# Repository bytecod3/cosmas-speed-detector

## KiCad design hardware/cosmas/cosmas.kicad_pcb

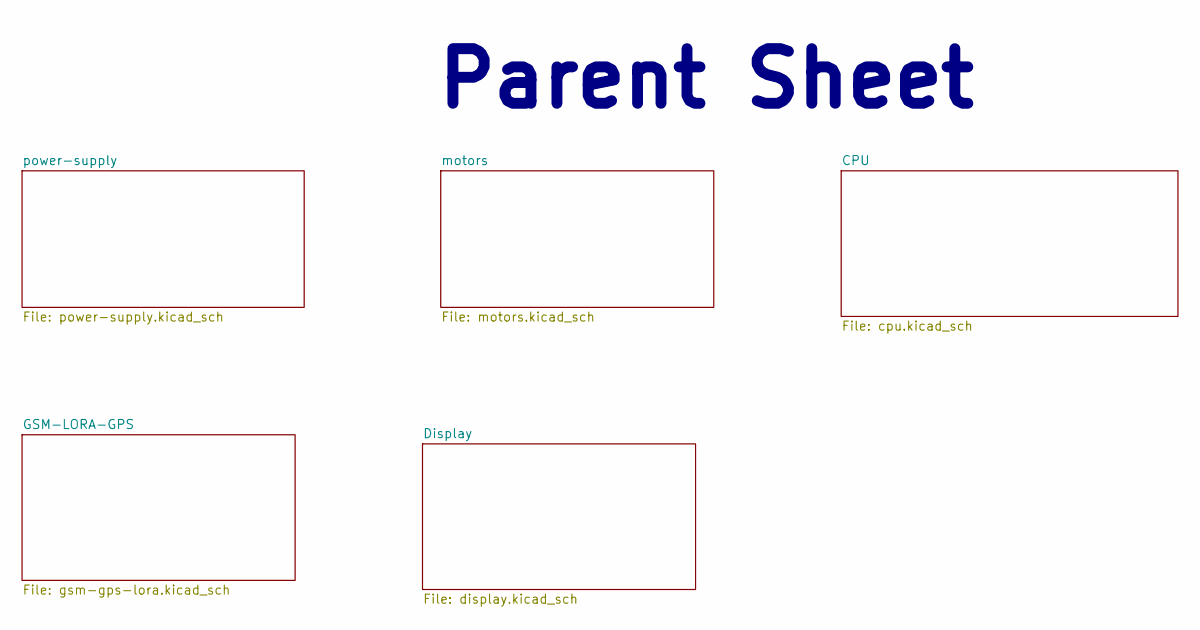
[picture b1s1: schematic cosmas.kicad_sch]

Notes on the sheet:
Parent Sheet

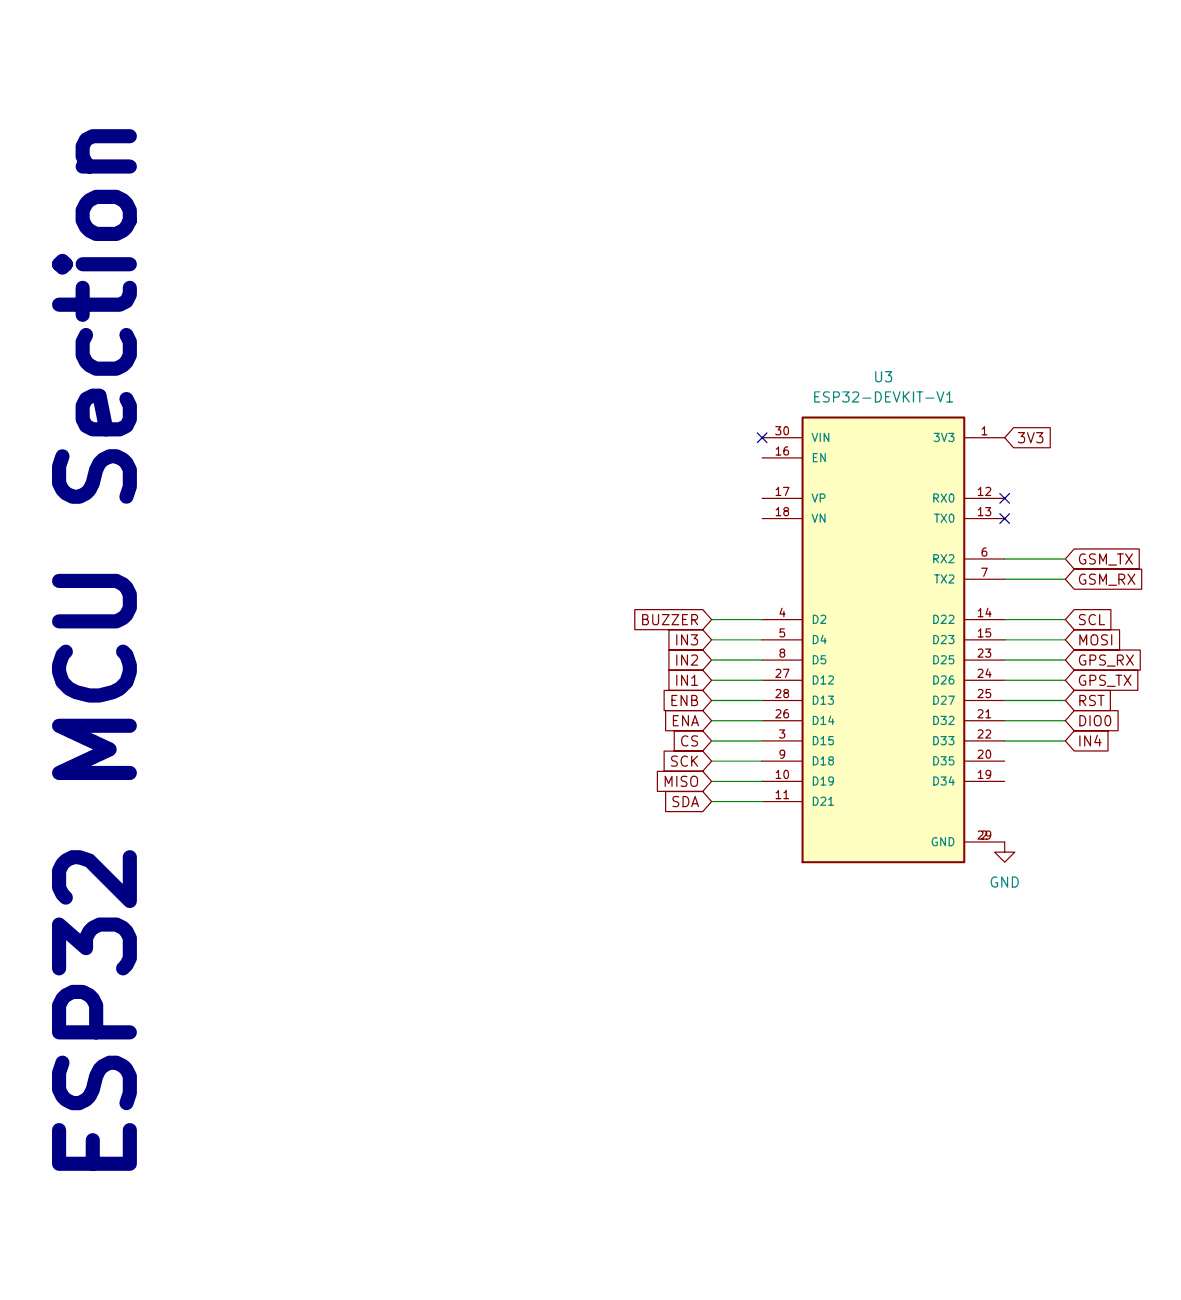
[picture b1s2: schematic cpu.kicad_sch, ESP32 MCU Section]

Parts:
U3: ESP32-DEVKIT-V1; MODULE_ESP32_DEVKIT_V1; PARTREV N/A

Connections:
3V3: U3.1 (3V3); also elsewhere on the board
BUZZER: U3.4 (D2); also elsewhere on the board
CS: U3.3 (D15); also elsewhere on the board
DIO0: U3.21 (D32); also elsewhere on the board
ENA: U3.26 (D14); also elsewhere on the board
ENB: U3.28 (D13); also elsewhere on the board
GND: U3.2 (GND), U3.29 (GND); also elsewhere on the board
GPS_RX: U3.23 (D25); also elsewhere on the board
GPS_TX: U3.24 (D26); also elsewhere on the board
GSM_RX: U3.7 (TX2); also elsewhere on the board
GSM_TX: U3.6 (RX2); also elsewhere on the board
IN1: U3.27 (D12); also elsewhere on the board
IN2: U3.8 (D5); also elsewhere on the board
IN3: U3.5 (D4); also elsewhere on the board
IN4: U3.22 (D33); also elsewhere on the board
MISO: U3.10 (D19); also elsewhere on the board
MOSI: U3.15 (D23); also elsewhere on the board
RST: U3.25 (D27); also elsewhere on the board
SCK: U3.9 (D18); also elsewhere on the board
SCL: U3.14 (D22); also elsewhere on the board
SDA: U3.11 (D21); also elsewhere on the board

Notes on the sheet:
ESP32 MCU Section

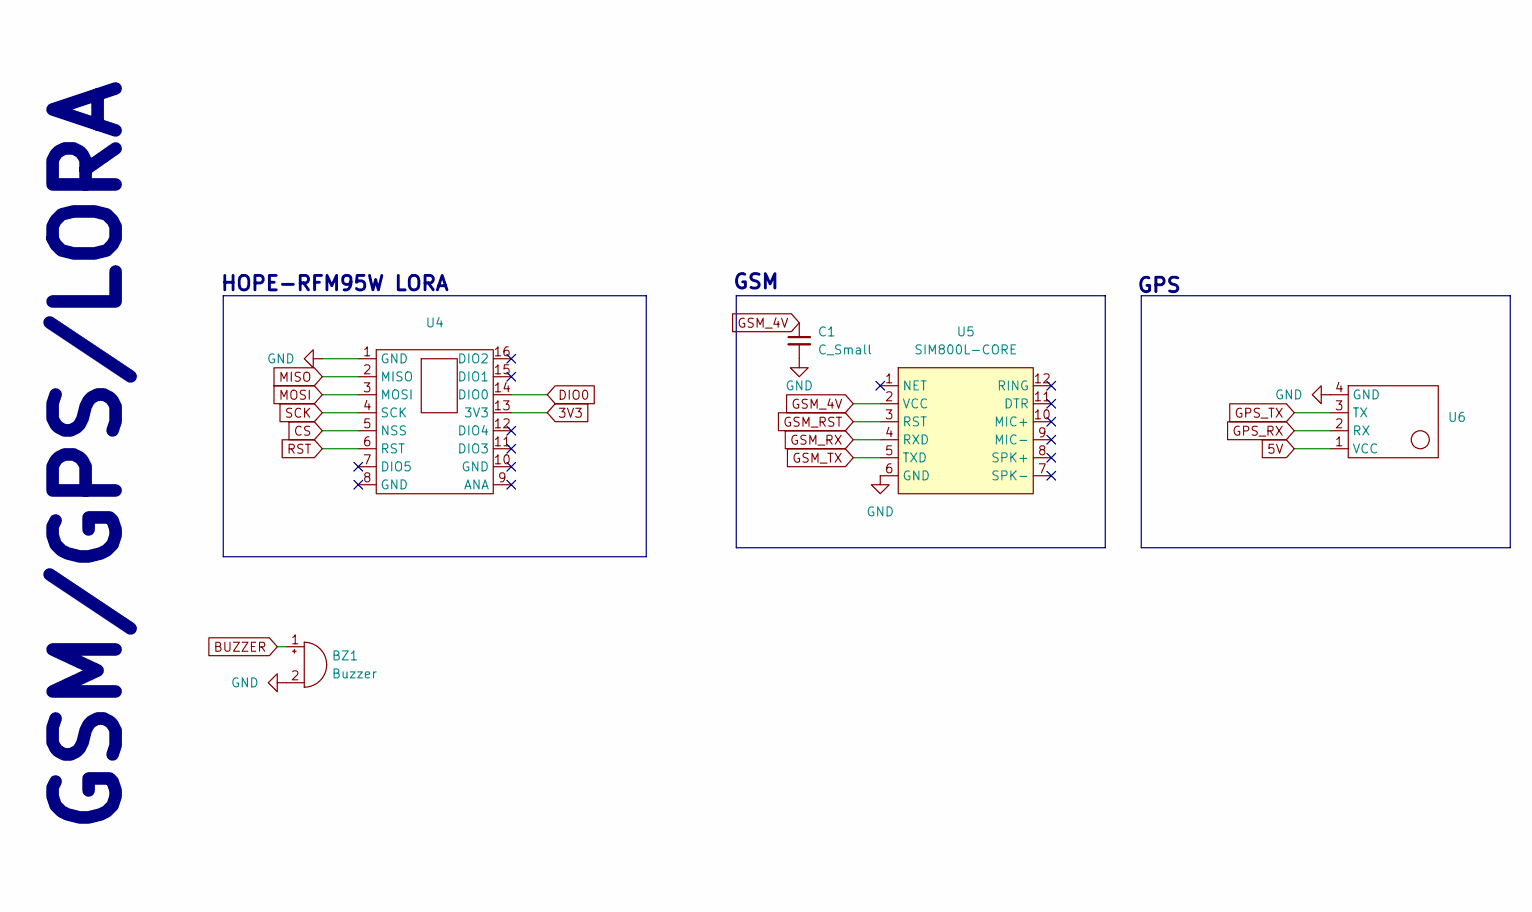
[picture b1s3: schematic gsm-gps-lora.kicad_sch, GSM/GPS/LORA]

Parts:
BZ1: Buzzer; MagneticBuzzer_PUI_AT-0927-TT-6-R
C1: C_Small; CP_Radial_D4.0mm_P2.00mm
U4: XCVR_RFM95W-915S2
U5: SIM800L-CORE
U6: NEO-6M-GPS-MODULE

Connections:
3V3: U4.13 (3V3); also elsewhere on the board
5V: U6.1 (VCC); also elsewhere on the board
BUZZER: BZ1.1 (+); also elsewhere on the board
CS: U4.5 (NSS); also elsewhere on the board
DIO0: U4.14 (DIO0); also elsewhere on the board
GND: BZ1.2 (-), C1.2, U4.1 (GND), U5.6 (GND), U6.4 (GND); also elsewhere on the board
GPS_RX: U6.2 (RX); also elsewhere on the board
GPS_TX: U6.3 (TX); also elsewhere on the board
GSM_4V: C1.1, U5.2 (VCC); also elsewhere on the board
GSM_RST: U5.3 (RST)
GSM_RX: U5.4 (RXD); also elsewhere on the board
GSM_TX: U5.5 (TXD); also elsewhere on the board
MISO: U4.2 (MISO); also elsewhere on the board
MOSI: U4.3 (MOSI); also elsewhere on the board
RST: U4.6 (RST); also elsewhere on the board
SCK: U4.4 (SCK); also elsewhere on the board

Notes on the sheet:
HOPE-RFM95W LORA
GPS
GSM
GSM/GPS/LORA

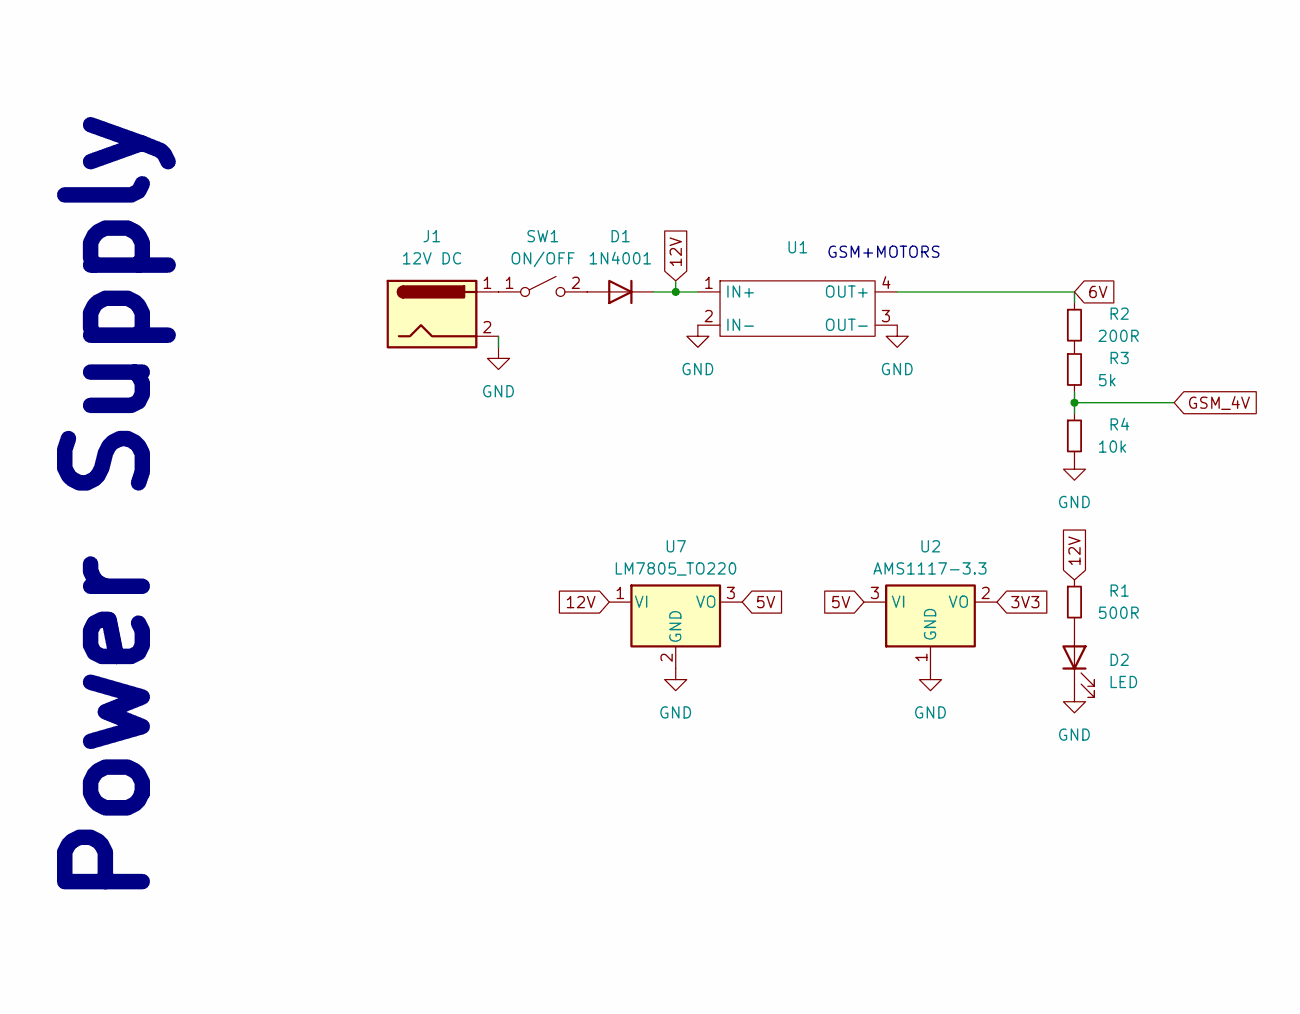
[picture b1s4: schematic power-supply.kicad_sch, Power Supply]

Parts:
D1: 1N4001; D_DO-41_SOD81_P10.16mm_Horizontal
D2: LED; LED_D3.0mm
J1: 12V DC; BarrelJack_Kycon_KLDX-0202-xC_Horizontal
R1: 500R; R_Axial_DIN0309_L9.0mm_D3.2mm_P15.24mm_Horizontal
R2: 200R; R_Axial_DIN0309_L9.0mm_D3.2mm_P15.24mm_Horizontal
R3: 5k; R_Axial_DIN0309_L9.0mm_D3.2mm_P15.24mm_Horizontal
R4: 10k; R_Axial_DIN0309_L9.0mm_D3.2mm_P15.24mm_Horizontal
SW1: ON/OFF; SW_Push_2P2T_Toggle_CK_PVA2OAH5xxxxxxV2
U1: LM2596-BUCK-CONVERTER
U2: AMS1117-3.3; SOT-223-3_TabPin2
U7: LM7805_TO220; TO-220-3_Vertical

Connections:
3V3: U2.2 (VO); also elsewhere on the board
5V: U2.3 (VI), U7.3 (VO); also elsewhere on the board
6V: R2.1, U1.4 (OUT+); also elsewhere on the board
12V: D1.1 (K), R1.1, U1.1 (IN+), U7.1 (VI)
GND: D2.1 (K), J1.2, R4.2, U1.2 (IN-), U1.3 (OUT-), U2.1 (GND), U7.2 (GND); also elsewhere on the board
GSM_4V: R3.2, R4.1; also elsewhere on the board
unnamed: D1.2 (A), SW1.2 (B)
unnamed: D2.2 (A), R1.2
unnamed: R2.2, R3.1
unnamed: J1.1, SW1.1 (A)

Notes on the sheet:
GSM+MOTORS
Power Supply

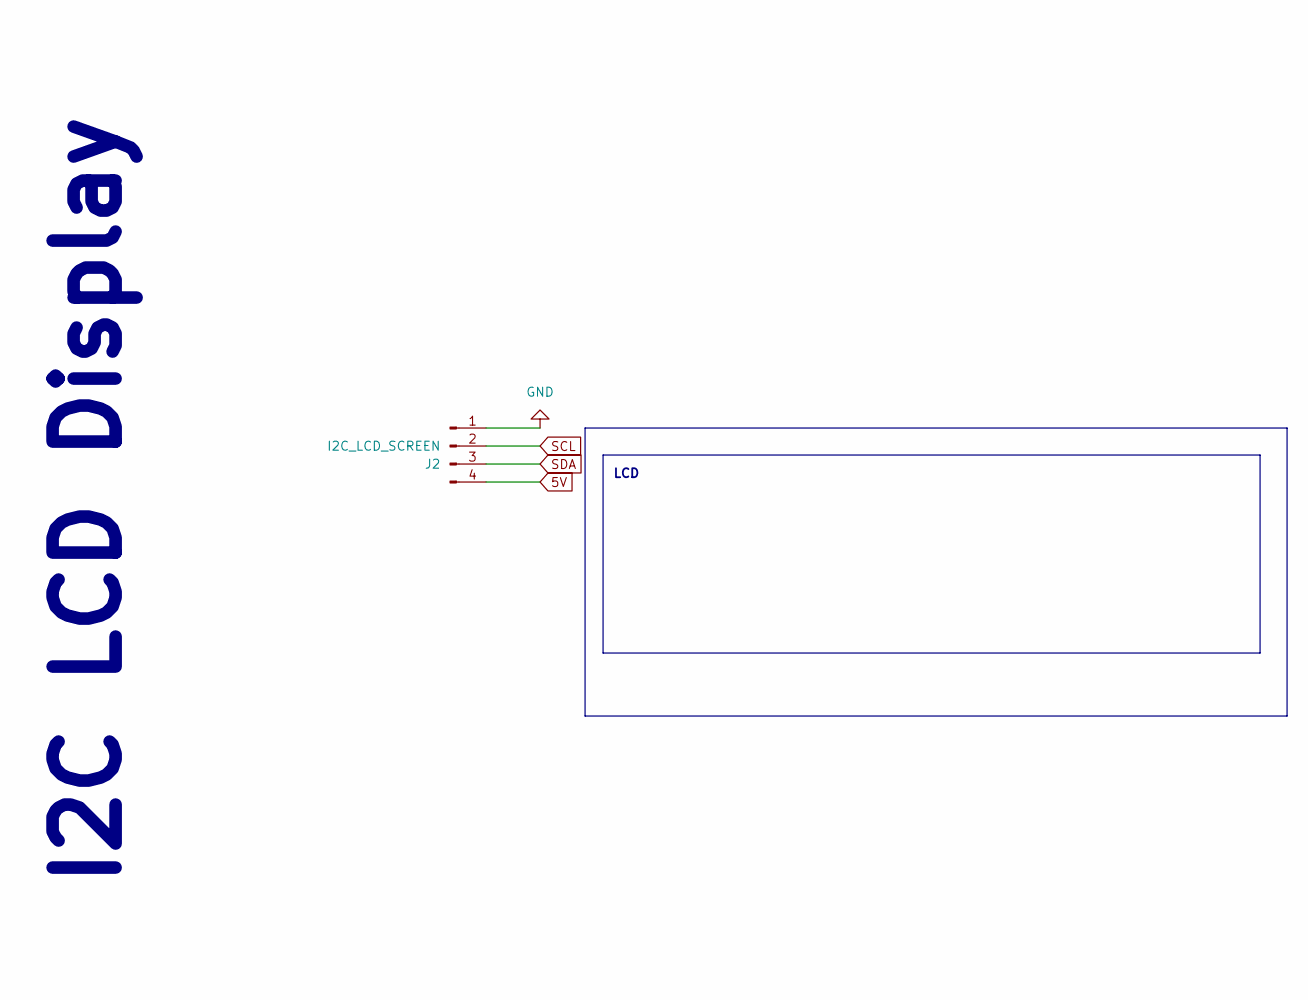
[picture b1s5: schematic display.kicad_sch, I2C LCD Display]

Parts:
J2: I2C_LCD_SCREEN; PinHeader_1x04_P2.54mm_Vertical

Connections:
5V: J2.4; also elsewhere on the board
GND: J2.1; also elsewhere on the board
SCL: J2.2; also elsewhere on the board
SDA: J2.3; also elsewhere on the board

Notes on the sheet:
LCD
I2C LCD Display

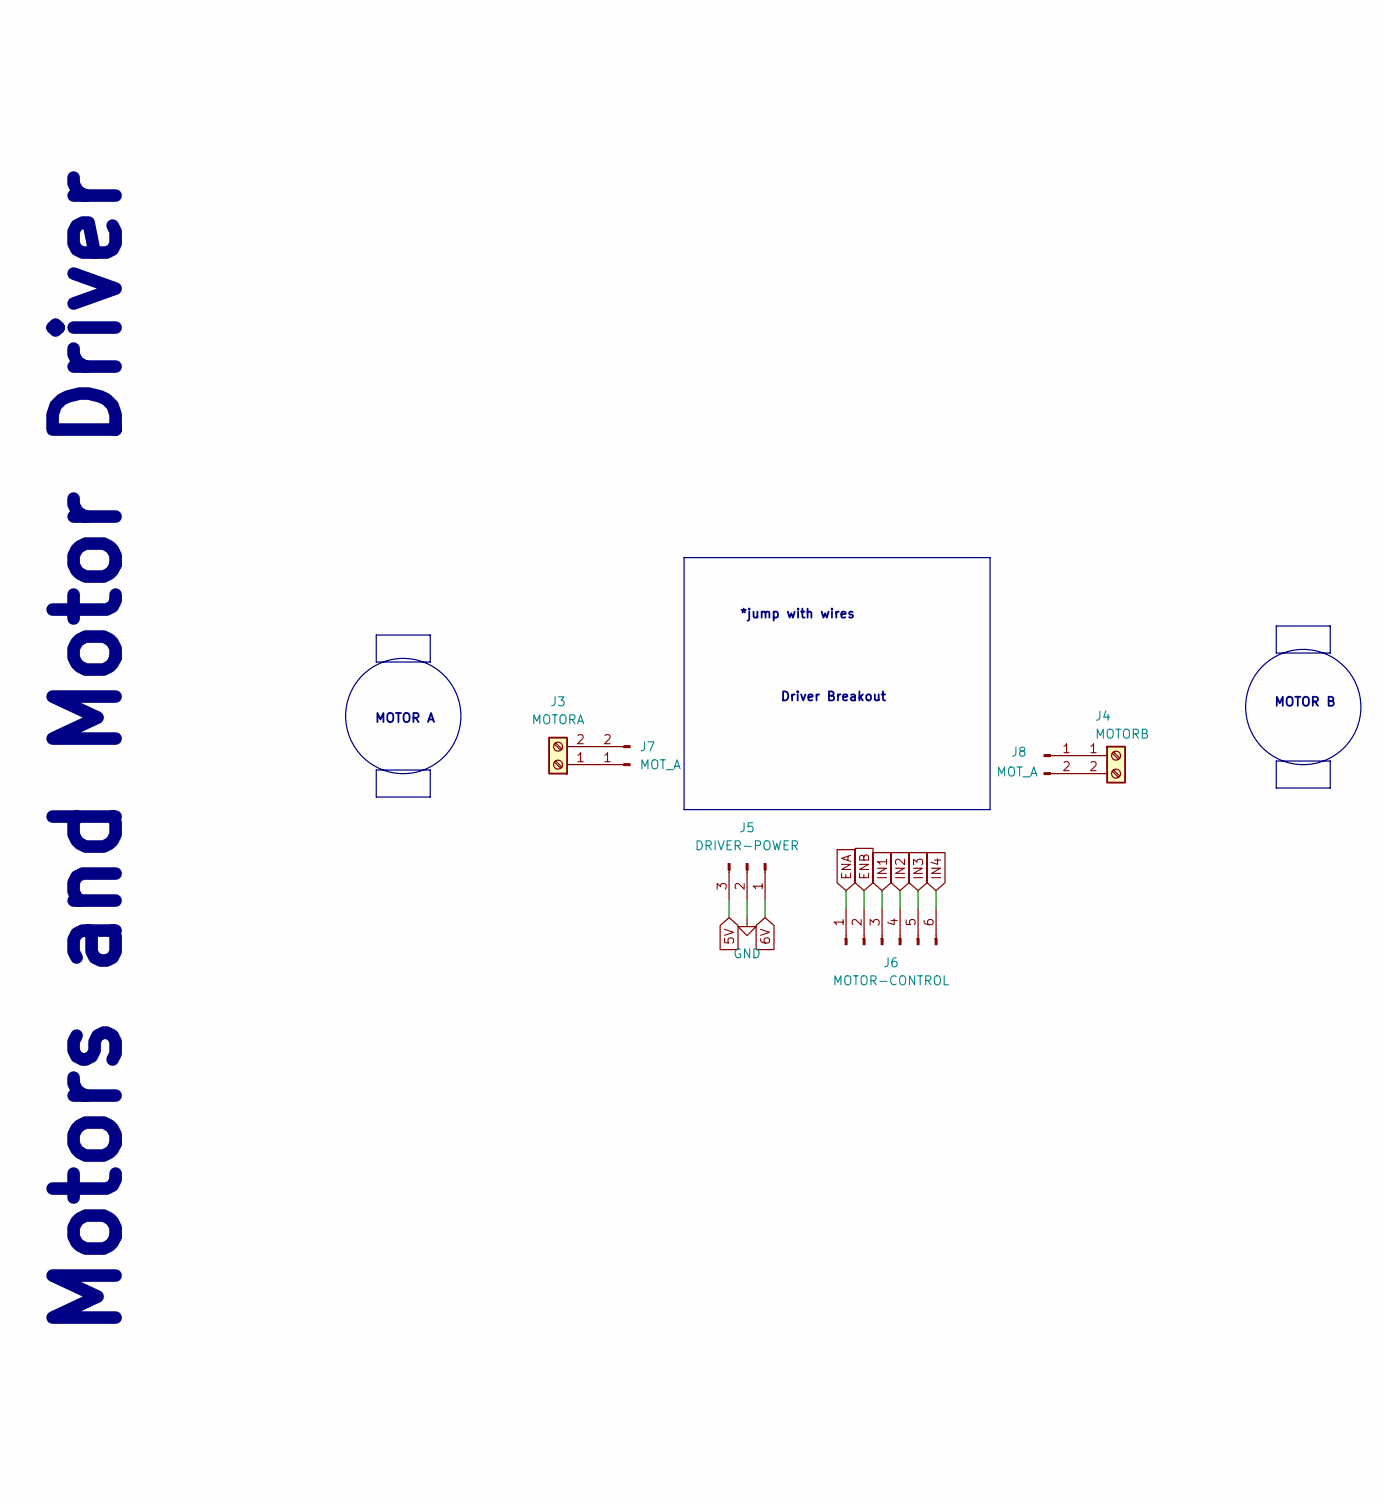
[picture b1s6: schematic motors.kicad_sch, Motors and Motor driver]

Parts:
J3: MOTORA; TerminalBlock_bornier-2_P5.08mm
J4: MOTORB; TerminalBlock_bornier-2_P5.08mm
J5: DRIVER-POWER; PinHeader_1x03_P2.54mm_Vertical
J6: MOTOR-CONTROL; PinHeader_1x06_P2.54mm_Vertical
J7, J8: MOT_A; PinHeader_1x02_P2.54mm_Vertical

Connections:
5V: J5.3; also elsewhere on the board
6V: J5.1; also elsewhere on the board
ENA: J6.1; also elsewhere on the board
ENB: J6.2; also elsewhere on the board
GND: J5.2; also elsewhere on the board
IN1: J6.3; also elsewhere on the board
IN2: J6.4; also elsewhere on the board
IN3: J6.5; also elsewhere on the board
IN4: J6.6; also elsewhere on the board
unnamed: J3.1, J7.1
unnamed: J3.2, J7.2
unnamed: J4.1, J8.1
unnamed: J4.2, J8.2

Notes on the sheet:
Motors and Motor Driver
Driver Breakout
MOTOR A
MOTOR B
*jump with wires

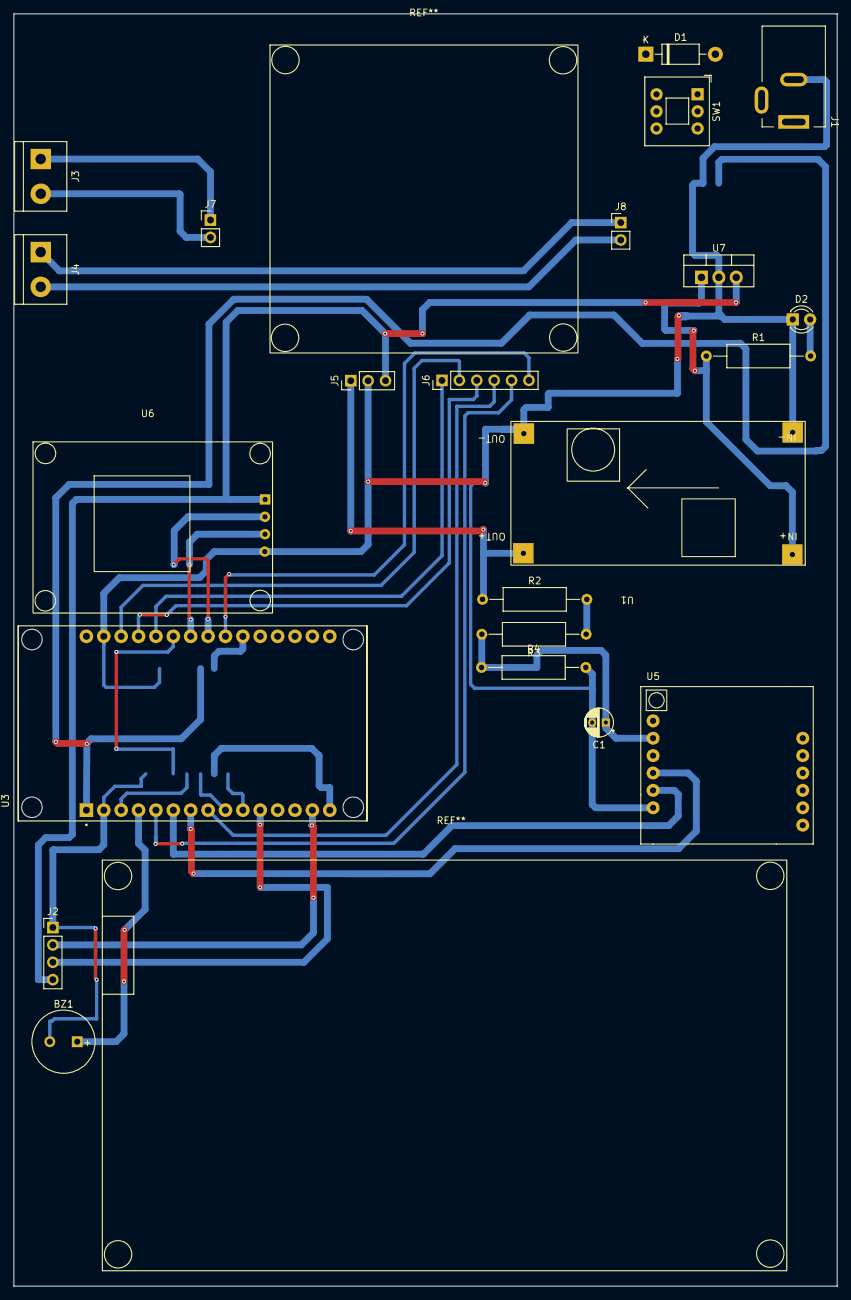
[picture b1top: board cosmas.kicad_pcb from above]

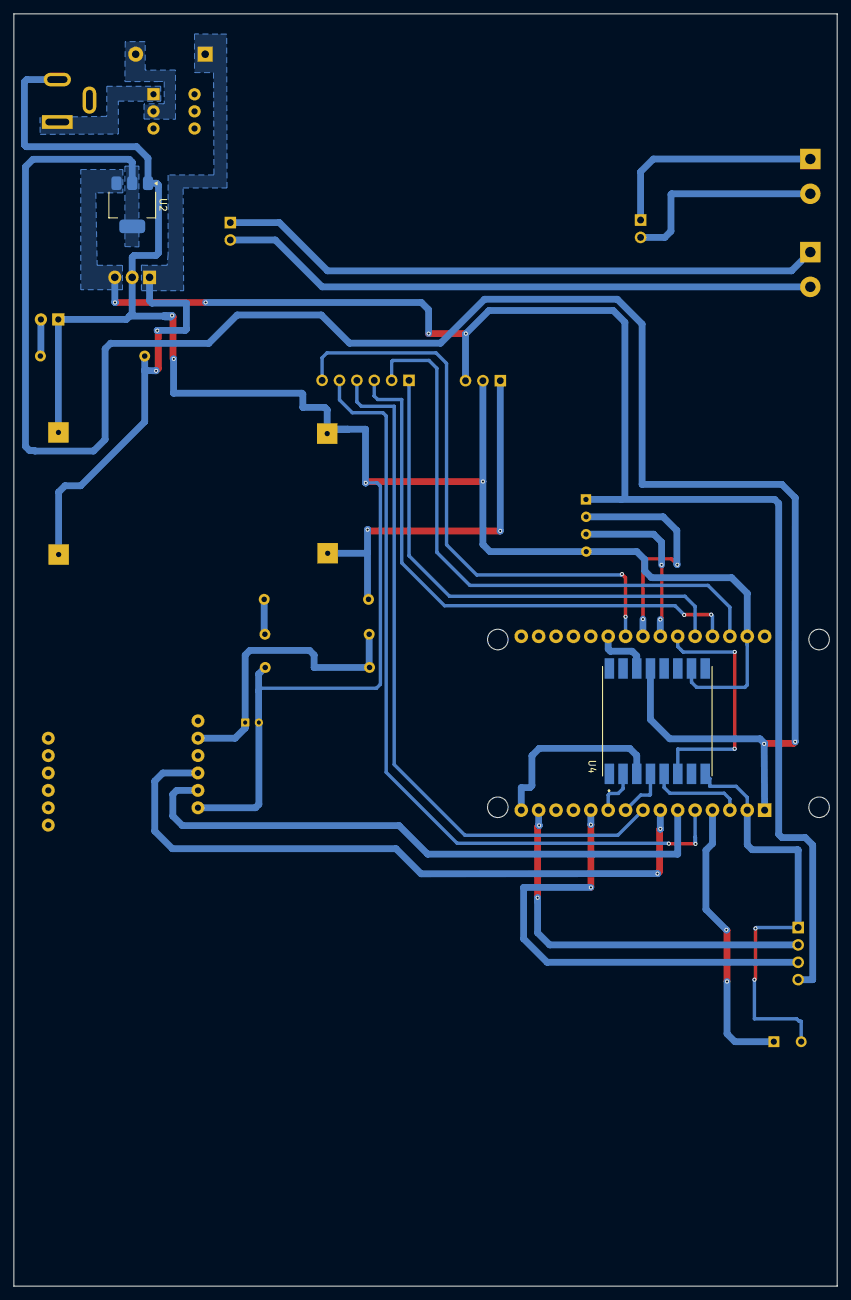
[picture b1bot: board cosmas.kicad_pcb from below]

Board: 2 copper layers, 120.3 x 185.9 mm, 24 parts (2 on the bottom side), 33 nets.

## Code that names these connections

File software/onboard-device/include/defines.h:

#ifndef DEFINES_H
#define DEFINES_H

#define DEBUG 1

#if DEBUG
#define debug(x)   Serial.print(x);
#define debugln(x)  Serial.println(x);
#define debugf(x, y) Serial.printf(x, y)

#else 
#define debug(x) 
#define debugln(x)  
#endif // END DEBUG


/* LCD defines  */
#define LCD_ADDR    0x27
#define LCD_ROWS    4
#define LCD_COLS    20

#define BAUD            115200
#define GPS_BAUD        9600
#define GSM_BAUD        9600
#define GPS_RX          26
#define GPS_TX          25
#define BUZZER          2
#define BUZZ_DELAY      200
#define STARTUP_DELAY   3000

/* LORA pins */
#define MOSI    23
#define MISO    19
#define SCK     18
#define NSS     15
#define RESET   27
#define DIO0    32
#define LORA_FREQUENCY 868E6

#define DECEL_DELAY 20  // milliseconds to delay when decelerating

#define EN1_A 14
#define EN1_B 13
#define IN1_1 12
#define IN1_2 5
#define IN1_3 4
#define IN1_4 33
#define M1_PWM
#define MATH_PI 3.142
#define BLACKSPOT_RADIUS 3
#define BLACKSPOT_SPEED_LIMIT 120 // PWM values
#define NORMAL_SPEED 240

#define NUM_BLACKSPOTS 4

// for different blackspot areas, different speed 
#define BLACKSPOT1_SPEED    90 // A BLACKSPOT
#define BLACKSPOT2_SPEED    100
#define BLACKSPOT3_SPEED    200
#define BLACKSPOT4_SPEED    120 // A BLACKSPOT

/*============================GSM VARIABLES=============================*/
#define GSM_RX 16
#define GSM_TX 17

#define TAMPER_SWITCH 36

#endif

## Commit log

2024-11-14 adds code dependencies
2024-11-14 adds LCD working code
2024-11-14 updates net labels
2024-11-17 adds OBC PCB
2024-11-23 updates GPS code
2025-01-01 adds motor driver
2025-01-01 adds motor speed control
2025-01-01 adds hardware serial for gps
2025-01-01 adds Haversine distance in km
2025-01-01 adds geofencing
2025-01-06 adds lora TX
2025-01-06 adds tamper checking
2025-01-08 final changes
2025-01-24 final code automated
2025-01-24 final working code
2025-01-24 final working code automated
